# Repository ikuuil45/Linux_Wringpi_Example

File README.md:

# Linux_Wringpi_Example
A.URL
https://github.com/WiringPi/WiringPi  //SDK 源码SDK 动态库

B.Example
1）Key interpet //已经完善

2）MPU6050 Example 数据终端读取 //已经完善

3）RGB Example //已经完善 中断 轮询 多进程

4）SSD1306 显示字符矩阵基本驱动

5）SSD1306 OLED刷新视频基于IIC //以及完善

C.SOP

一.Git仓库地址
1.Address:
https://github.com/WiringPi/WiringPi     //git到本地即可，目前作者最新版本是2.70

wish@raspberrypi:/WiringPi/wiringPi $ gpio -v
gpio version: 2.70
Copyright (c) 2012-2018 Gordon Henderson
This is free software with ABSOLUTELY NO WARRANTY.
For details type: gpio -warranty

Raspberry Pi Details:
  Type: Pi 4B, Revision: 05, Memory: 8192MB, Maker: Sony
  * Device tree is enabled.
  *--> Raspberry Pi 4 Model B Rev 1.5
  * This Raspberry Pi supports user-level GPIO access.
wish@raspberrypi:/WiringPi/wiringPi $

2.SDK介绍
wish@raspberrypi:/WiringPi $ ls
build  COPYING.LESSER  debian  debian-template  devLib  examples  gpio  INSTALL  newVersion  People  pins  README.md  update  VERSION  version.h  wiringPi  wiringPiD
wish@raspberrypi:/WiringPi $
1)WiringPi_SDK：
在软件开发中，SDK（Software Development Kit）是一组工具、库和文档的集合，用于帮助开发人员创建特定平台或技术的应用程序。

2)Build:
  构建配置：构建文件用于配置项目的构建过程，包括编译源代码、链接库文件、生成可执行文件等。它定义了编译器选项、依赖关系、目标文件路径等构建相关的设置。

  自动化构建：构建文件可以用于自动化构建过程，通过简单的命令或脚本，可以执行一系列构建步骤，从而减少手动操作的工作量。这样可以提高开发效率，并确保每次构建都是一致的。

  依赖管理：构建文件可以指定项目所依赖的其他库或模块，以及它们的版本要求。这样，在构建过程中，构建工具可以自动下载、编译和链接这些依赖项，确保项目能够正确地使用它们。

  跨平台支持：构建文件可以针对不同的操作系统和平台进行配置，以适应不同的开发环境。通过构建文件，可以定义不同平台上的编译器选项、库文件路径等，从而实现跨平台的开发和构建。

3)devLib 
   已经支持的设备相关源代码和链接库

4)examples
  示例代码
  Makefile

5)INSTALL
   For help and support see:

 * https://github.com/WiringPi/WiringPi/issues
 * https://discord.gg/SM4WUVG

 * wiringPi originally created by Gordon Henderson
 * https://projects.drogon.net/

6)newVersion 
    # This file is part of wiringPi:
    #  A "wiring" library for the Raspberry Pi
    
    #    wiringPi is free software: you can redistribute it and/or modify
    #    it under the terms of the GNU Lesser General Public License as published by
    #    the Free Software Foundation, either version 3 of the License, or
    #    (at your option) any later version.
    #
    #    wiringPi is distributed in the hope that it will be useful,
    #    but WITHOUT ANY WARRANTY; without even the implied warranty of
    #    MERCHANTABILITY or FITNESS FOR A PARTICULAR PURPOSE.  See the
    #    GNU Lesser General Public License for more details.
    #
    #    You should have received a copy of the GNU Lesser General Public License
    #    along with wiringPi.  If not, see <http://www.gnu.org/licenses/>.

7)People 
        Just a quick note to some people who've provided help, suggestions,
        bug-fixes, etc. along the way...

8)wiringPi
源码

9)Others
二.硬件接口对应
1按照wringpi的对应关系
const int Red_Pin=1; //wPi中的1

const int Green_Pin=4; //wPi中的4

const int Blue_Pin=5; //wPi中的5

wish@raspberrypi:/WiringPi/examples $ gpio readall
 +-----+-----+---------+------+---+---Pi 4B--+---+------+---------+-----+-----+
 | BCM | wPi |   Name  | Mode | V | Physical | V | Mode | Name    | wPi | BCM |
 +-----+-----+---------+------+---+----++----+---+------+---------+-----+-----+
 |     |     |    3.3v |      |   |  1 || 2  |   |      | 5v      |     |     |
 |   2 |   8 |   SDA.1 |   IN | 1 |  3 || 4  |   |      | 5v      |     |     |
 |   3 |   9 |   SCL.1 |   IN | 1 |  5 || 6  |   |      | 0v      |     |     |
 |   4 |   7 | GPIO. 7 |   IN | 1 |  7 || 8  | 1 | IN   | TxD     | 15  | 14  |
 |     |     |      0v |      |   |  9 || 10 | 1 | IN   | RxD     | 16  | 15  |
 |  17 |   0 | GPIO. 0 |   IN | 0 | 11 || 12 | 1 | OUT  | GPIO. 1 | 1   | 18  |
 |  27 |   2 | GPIO. 2 |   IN | 0 | 13 || 14 |   |      | 0v      |     |     |
 |  22 |   3 | GPIO. 3 |   IN | 0 | 15 || 16 | 0 | OUT  | GPIO. 4 | 4   | 23  |
 |     |     |    3.3v |      |   | 17 || 18 | 0 | OUT  | GPIO. 5 | 5   | 24  |
 |  10 |  12 |    MOSI |   IN | 0 | 19 || 20 |   |      | 0v      |     |     |
 |   9 |  13 |    MISO |   IN | 0 | 21 || 22 | 0 | IN   | GPIO. 6 | 6   | 25  |
 |  11 |  14 |    SCLK |   IN | 0 | 23 || 24 | 1 | IN   | CE0     | 10  | 8   |
 |     |     |      0v |      |   | 25 || 26 | 1 | IN   | CE1     | 11  | 7   |
 |   0 |  30 |   SDA.0 |   IN | 1 | 27 || 28 | 1 | IN   | SCL.0   | 31  | 1   |
 |   5 |  21 | GPIO.21 |   IN | 1 | 29 || 30 |   |      | 0v      |     |     |
 |   6 |  22 | GPIO.22 |   IN | 1 | 31 || 32 | 0 | IN   | GPIO.26 | 26  | 12  |
 |  13 |  23 | GPIO.23 |   IN | 0 | 33 || 34 |   |      | 0v      |     |     |
 |  19 |  24 | GPIO.24 |   IN | 0 | 35 || 36 | 0 | IN   | GPIO.27 | 27  | 16  |
 |  26 |  25 | GPIO.25 |   IN | 0 | 37 || 38 | 0 | IN   | GPIO.28 | 28  | 20  |
 |     |     |      0v |      |   | 39 || 40 | 0 | IN   | GPIO.29 | 29  | 21  |
 +-----+-----+---------+------+---+----++----+---+------+---------+-----+-----+
 | BCM | wPi |   Name  | Mode | V | Physical | V | Mode | Name    | wPi | BCM |
 +-----+-----+---------+------+---+---Pi 4B--+---+------+---------+-----+-----+

2.实物接线
比较混乱是因为还接了一个逻辑分析仪

三.已经验证的版本C源码
1.网上找到的初步版本代码
#include <wiringPi.h>
#include <stdio.h>
#include <stdlib.h>
#include <stdint.h>
#include <softPwm.h>

const int Red_Pin=1;
const int Green_Pin=4;
const int Blue_Pin=5;

void RGB_Color_Init()
{
    softPwmCreate(Red_Pin, 0, 255);
    softPwmCreate(Green_Pin, 0, 255);
    softPwmCreate(Blue_Pin, 0, 255);
    
}

int main()
{

  if(wiringPiSetup() == -1)//树莓派引脚初始化，返回-1则初始化失败
     {
        printf("Error!\n");
        return 1;
     }
     RGB_Color_Init();

    while(1)
    
    {
        //实现彩色渐变循环亮功能
        for(int i=0;i <= 255;i++)//实现彩色渐变循环亮功能
        {
            softPwmWrite(Red_Pin,255);//红
            softPwmWrite(Green_Pin,0);
            softPwmWrite(Blue_Pin,0);
            printf("RED\n");
            delay(10);
        }
            
         for(int i = 255; i>= 0; i--)
        {
            softPwmWrite(Red_Pin,230);//橙
            softPwmWrite(Green_Pin,20);
            softPwmWrite(Blue_Pin,0);
            printf("ORANGE\n");
            delay(10);
        }
       
         for(int i=0;i <= 255;i++)
        {
            softPwmWrite(Red_Pin,255);//黄
            softPwmWrite(Green_Pin,30);
            softPwmWrite(Blue_Pin,0);
            printf("YELLOW\n");
            delay(10);

        }

        for(int i = 255; i>= 0; i--)
        {
            softPwmWrite(Red_Pin,0);//绿
            softPwmWrite(Green_Pin,255);
            softPwmWrite(Blue_Pin,0);
            printf("GREEN\n");
            delay(10);
        }

        for(int i=0;i <= 255;i++)
        {
            softPwmWrite(Red_Pin,0);//青
            softPwmWrite(Green_Pin,250);
            softPwmWrite(Blue_Pin,154);
            printf("MedSpringGreen\n");
            delay(10);
        }

        for(int i = 255; i>= 0; i--)
        {
            softPwmWrite(Red_Pin,0);//蓝
            softPwmWrite(Green_Pin,0);
            softPwmWrite(Blue_Pin,255);
            printf("BLUE\n");
            delay(10);
        }

        for(int i=0;i <= 255;i++)
        {
            softPwmWrite(Red_Pin,139);//紫
            softPwmWrite(Green_Pin,0);
            softPwmWrite(Blue_Pin,139);
            printf("Purple\n");
            delay(10);
        }

    }
    return 0;

}

2.优化及调试过程
1）循环太多，采用二维数组优化。
   {
        //实现彩色渐变循环亮功能
        
        for (i=0; i < numColors; i++)
         {
            softPwmWrite(Red_Pin, colors[i][0]);
            softPwmWrite(Green_Pin, colors[i][1]);
            softPwmWrite(Blue_Pin, colors[i][2]);
            printf("%s\n", colorNames[i]);
            delay(1000);

         }
        printf("Color_Cycle_success\n");
        i=0;

    }

2）循环次数设置成了255次，直接干出那个二维数组的内存区域了，指针越界会发送段错误，采用sizeof动态采集
pwmrainbow.c: In function ‘main’:
pwmrainbow.c:42:9: warning: variable ‘i’ set but not used [-Wunused-but-set-var                                                                                                           iable]
   42 |     int i=0;
      |         ^
wish@raspberrypi:/WiringPi/examples $ ^C
wish@raspberrypi:/WiringPi/examples $
wish@raspberrypi:/WiringPi/examples $
wish@raspberrypi:/WiringPi/examples $ gcc -Wall -o pwmrainbow pwmrainbow.c -lwi                                                                                                           ringPi
pwmrainbow.c: In function ‘main’:
pwmrainbow.c:57:9: warning: statement with no effect [-Wunused-value]
   57 |         for (i; i <255; i++)
      |         ^~~
wish@raspberrypi:/WiringPi/examples $ gcc -Wall -o pwmrainbow pwmrainbow.c -lwi                                                                                                           ringPi
wish@raspberrypi:/WiringPi/examples $ ./pwmrainbow

3）char型数组无法放置长英文，采用char型指针读取颜色符号
wish@raspberrypi:/WiringPi/examples $ gcc -Wall -o pwmrainbow pwmrainbow.c -lwr                                                                                                           omhPi
pwmrainbow.c:23:5: error: excess elements in ‘char’ array initializer
   23 |     "Orange",
      |     ^~~~~~~~
pwmrainbow.c:23:5: note: (near initialization for ‘colorNames’)
pwmrainbow.c:24:5: error: excess elements in ‘char’ array initializer
   24 |     "Yellow",
      |     ^~~~~~~~
pwmrainbow.c:24:5: note: (near initialization for ‘colorNames’)
pwmrainbow.c:25:5: error: excess elements in ‘char’ array initializer
   25 |     "Green",
      |     ^~~~~~~
pwmrainbow.c:25:5: note: (near initialization for ‘colorNames’)
pwmrainbow.c:26:5: error: excess elements in ‘char’ array initializer
   26 |     "Cyan",
      |     ^~~~~~
pwmrainbow.c:26:5: note: (near initialization for ‘colorNames’)
pwmrainbow.c:27:5: error: excess elements in ‘char’ array initialize

char* colorNames[] =
 {
    "Red",
    "Orange",
    "Yellow",
    "Green",
    "Cyan",
    "Blue",
    "Purple"
};

3.优化后的代码【个人拙改】
#include <wiringPi.h>
#include <stdio.h>
#include <stdlib.h>
#include <stdint.h>
#include <softPwm.h>

const int Red_Pin=1;
const int Green_Pin=4;
const int Blue_Pin=5;
int i;
int colors[][3] =
 {
    {255, 0, 0},     // 红色
    {230, 20, 0},    // 橙色
    {255, 30, 0},    // 黄色
    {0, 255, 0},     // 绿色
    {0, 250, 154},   // 青色
    {0, 0, 255},     // 蓝色
    {139, 0, 139}    // 紫色
};
int numColors = sizeof(colors) / sizeof(colors[0]);

char* colorNames[] =
 {
    "Red",
    "Orange",
    "Yellow",
    "Green",
    "Cyan",
    "Blue",
    "Purple"
};

void RGB_Color_Init()
{
    softPwmCreate(Red_Pin, 0, 255);
    softPwmCreate(Green_Pin, 0, 255);
    softPwmCreate(Blue_Pin, 0, 255);  
}

int main()
{

     if(wiringPiSetup() == -1)//树莓派引脚初始化，返回-1则初始化失败
     {
        printf("Error!\n");
        return 1;
     }
     RGB_Color_Init();

    while(1)
    
    {
        //实现彩色渐变循环亮功能
        
        for (i=0; i < numColors; i++)
         {
            softPwmWrite(Red_Pin, colors[i][0]);
            softPwmWrite(Green_Pin, colors[i][1]);
            softPwmWrite(Blue_Pin, colors[i][2]);
            printf("%s\n", colorNames[i]);
            delay(1000);

         }
        printf("Color_Cycle_success\n");
        i=0;

    }

    return 0;

}

四.编译过程
1.过程及原理
gcc -Wall -o pwmrainbow pwmrainbow.c -lwiringPi
 

这个命令是使用gcc编译器来编译一个名为pwmrainbow.c的源代码文件，并生成一个可执行文件名为pwmrainbow。下面是对该命令中各个参数的解释：

gcc: 是GNU Compiler Collection（GNU编译器集合）的缩写，它是一种常用的编译器工具。
-Wall: 是gcc的一个编译选项，表示开启所有警告信息。这样可以让编译器在编译过程中输出更多的警告信息，帮助开发者发现潜在的问题。
-o pwmrainbow: 是指定生成的可执行文件的名称为pwmrainbow。-o是gcc的一个选项，用于指定输出文件的名称。
pwmrainbow.c: 是要编译的源代码文件的名称，这里假设源代码文件为pwmrainbow.c。
-lwiringPi: 是指定链接wiringPi库。-l是gcc的一个选项，用于指定需要链接的库文件。这里假设需要链接的库文件为wiringPi。
综上所述，该命令的作用是将pwmrainbow.c源代码文件编译成一个可执行文件pwmrainbow，并在链接过程中使用wiringPi库。编译过程中会开启所有警告信息的输出。

2.动态和静态编译
动态库和静态库是在软件开发中常用的两种库文件形式，它们有不同的工作原理。

静态库（Static Library）： 静态库是一组预编译的目标代码文件的集合，这些文件包含了函数、变量和其他可供程序使用的资源。在编译时，静态库的代码会被完整地复制到最终的可执行文件中。当程序运行时，所有需要的函数和资源都已经包含在可执行文件中，因此程序可以独立运行，不依赖于外部的库文件。静态库的优点是使用简单，不需要额外的依赖，但缺点是每个可执行文件都会包含一份完整的库代码，导致可执行文件体积较大。

动态库（Dynamic Library）： 动态库是一组共享的目标代码文件，它们在程序运行时被加载到内存中，并可以被多个程序共享使用。在编译时，可执行文件只包含对动态库的引用，而不包含实际的库代码。当程序运行时，操作系统会根据需要将动态库加载到内存中，并建立与可执行文件之间的链接。动态库的优点是节省内存空间，多个程序可以共享同一个库，更新库时只需替换动态库文件而无需重新编译可执行文件。但缺点是需要依赖外部的库文件，如果动态库版本不兼容或缺失，程序可能无法正常运行。

总结起来，静态库在编译时被完整地复制到可执行文件中，而动态库在程序运行时被加载到内存中。静态库适合于独立运行的程序，而动态库适合于多个程序共享使用的情况。选择使用哪种库取决于具体的需求和项目要求。

3.依赖的动态so
libwiringPi.so.2.70 

wish@raspberrypi:/WiringPi/wiringPi $ ls
ads1115.c       drcNet.o     htu21d.o             mcp23008.c     mcp23017.o    mcp3002.c  mcp4802.c     pcf8591.o     rht03.h      softServo.h  wiringPiI2C.c   wiringSerial.o
ads1115.h       drcSerial.c  libwiringPi.so.2.70  mcp23008.h     mcp23s08.c    mcp3002.h  mcp4802.h     piHiPri.c     rht03.o      softTone.c   wiringPiI2C.h   wiringShift.c
ads1115.o       drcSerial.h  Makefile             mcp23008.o     mcp23s08.h    mcp3002.o  mcp4802.o     piHiPri.o     sn3218.c     softTone.h   wiringPiI2C.o   wiringShift.h
bmp180.c        drcSerial.o  max31855.c           mcp23016.c     mcp23s08.o    mcp3004.c  noMoreStatic  piThread.c    sn3218.h     softTone.o   wiringPi.o      wiringShift.o
bmp180.h        ds18b20.c    max31855.h           mcp23016.h     mcp23s17.c    mcp3004.h  pcf8574.c     piThread.o    sn3218.o     sr595.c      wiringPiSPI.c   wpiExtensions.c
bmp180.o        ds18b20.h    max31855.o           mcp23016.o     mcp23s17.h    mcp3004.o  pcf8574.h     pseudoPins.c  softPwm.c    sr595.h      wiringPiSPI.h   wpiExtensions.h
COPYING.LESSER  ds18b20.o    max5322.c            mcp23016reg.h  mcp23s17.o    mcp3422.c  pcf8574.o     pseudoPins.h  softPwm.h    sr595.o      wiringPiSPI.o   wpiExtensions.o
drcNet.c        htu21d.c     max5322.h            mcp23017.c     mcp23x0817.h  mcp3422.h  pcf8591.c     pseudoPins.o  softPwm.o    wiringPi.c   wiringSerial.c
drcNet.h        htu21d.h     max5322.o            mcp23017.h     mcp23x08.h    mcp3422.o  pcf8591.h     rht03.c       softServo.c  wiringPi.h   wiringSerial.h
wish@raspberrypi:/WiringPi/wiringPi $ ^C

五.实现
1.编译运行

wish@raspberrypi:/WiringPi/examples $ ./pwmrainbow
Red
Orange
Yellow
Green
Cyan
Blue
Purple
^C

2.逻辑分析仪PWM波形

 3.实现效果
https://www.bilibili.com/video/BV1cF411X7p7/?spm_id_from=333.999.0.0

​

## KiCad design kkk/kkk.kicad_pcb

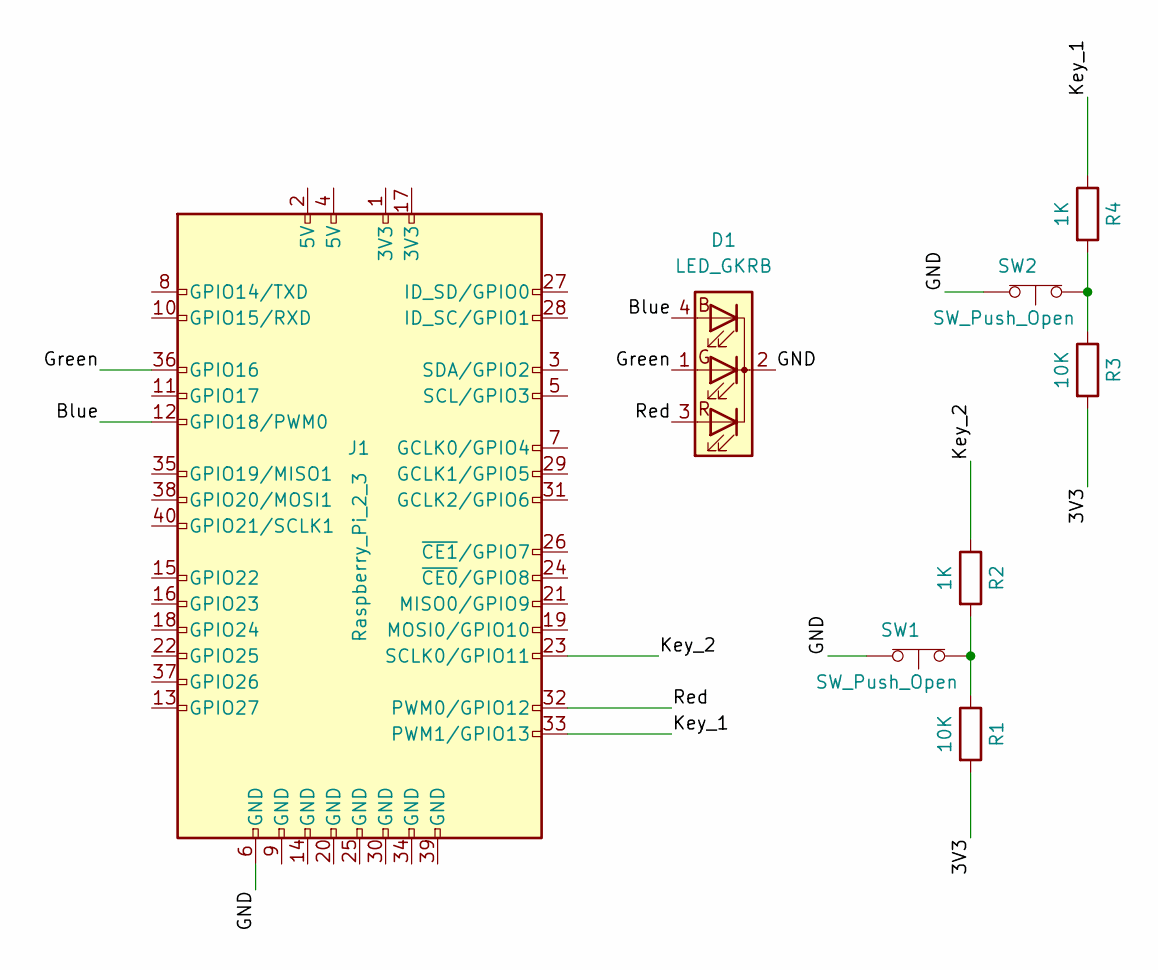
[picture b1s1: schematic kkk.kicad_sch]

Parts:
D1: LED_GKRB; LED_D5.0mm-4_RGB
J1: Raspberry_Pi_2_3; Raspberry_Pi_Zero_Socketed_THT_FaceDown_MountingHoles
R1, R3: 10K; R_Axial_DIN0411_L9.9mm_D3.6mm_P15.24mm_Horizontal
R2, R4: 1K; R_Axial_DIN0411_L9.9mm_D3.6mm_P15.24mm_Horizontal
SW1, SW2: SW_Push_Open; SW_DIP_SPSTx01_Slide_9.78x4.72mm_W7.62mm_P2.54mm

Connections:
/3V3: R1.2, R3.2
/Blue: D1.4 (BA), J1.12 (GPIO18/PWM0)
/GND: D1.2 (K), J1.6 (GND), SW1.2 (B), SW2.2 (B)
/Green: D1.1 (GA), J1.36 (GPIO16)
/Key_1: J1.33 (PWM1/GPIO13), R4.1
/Key_2: J1.23 (SCLK0/GPIO11), R2.1
/Red: D1.3 (RA), J1.32 (PWM0/GPIO12)
unnamed: R1.1, R2.2, SW1.1 (A)
unnamed: R3.1, R4.2, SW2.1 (A)

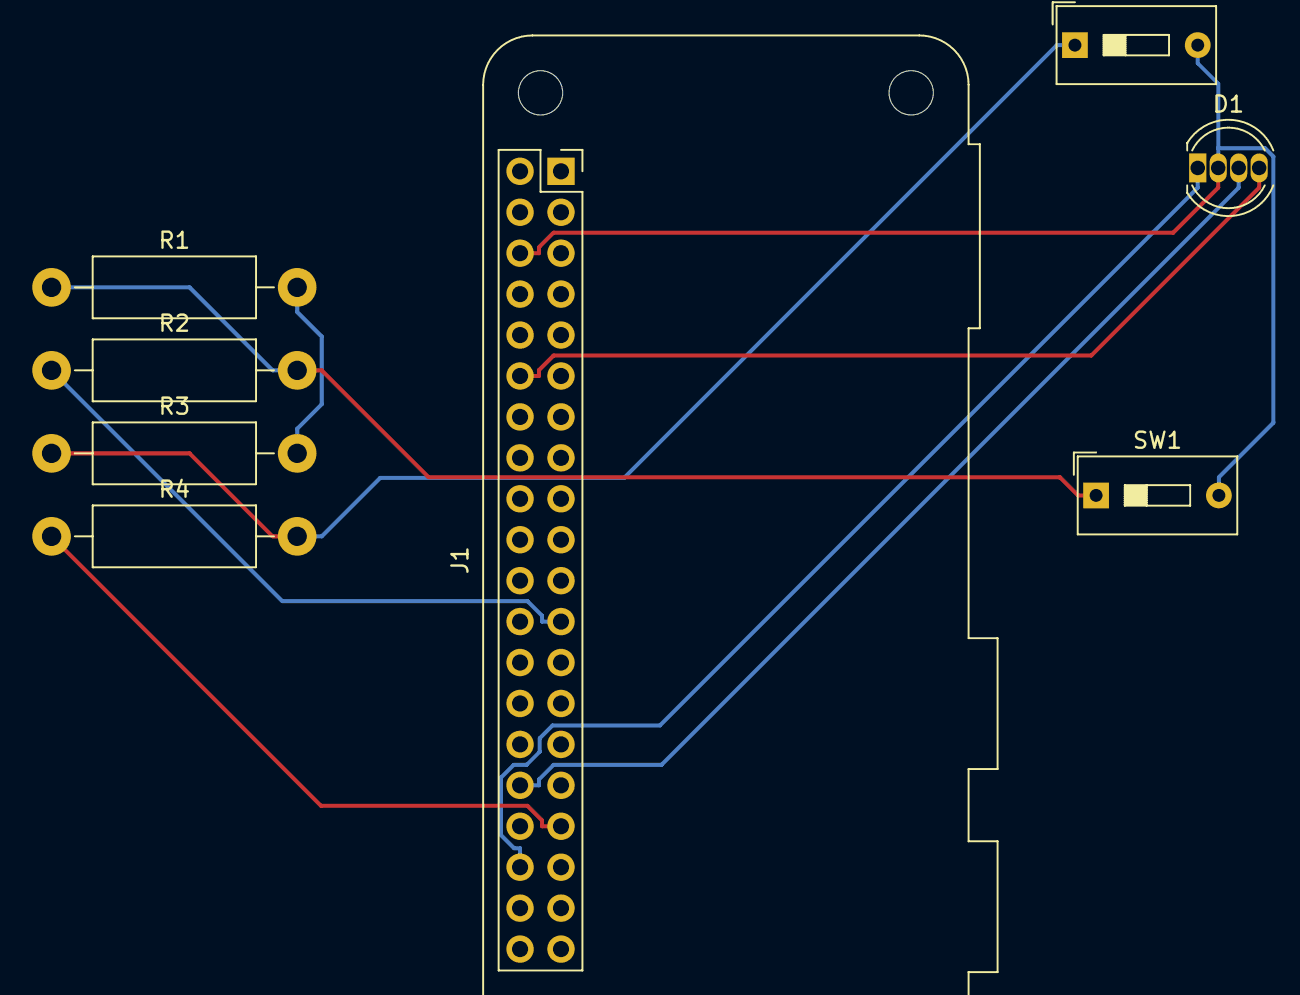
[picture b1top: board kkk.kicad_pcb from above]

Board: 2 copper layers, 8 parts (0 on the bottom side), 9 nets.

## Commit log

2023-09-21 Create SSD1306
2023-09-21 Create MPU6050
